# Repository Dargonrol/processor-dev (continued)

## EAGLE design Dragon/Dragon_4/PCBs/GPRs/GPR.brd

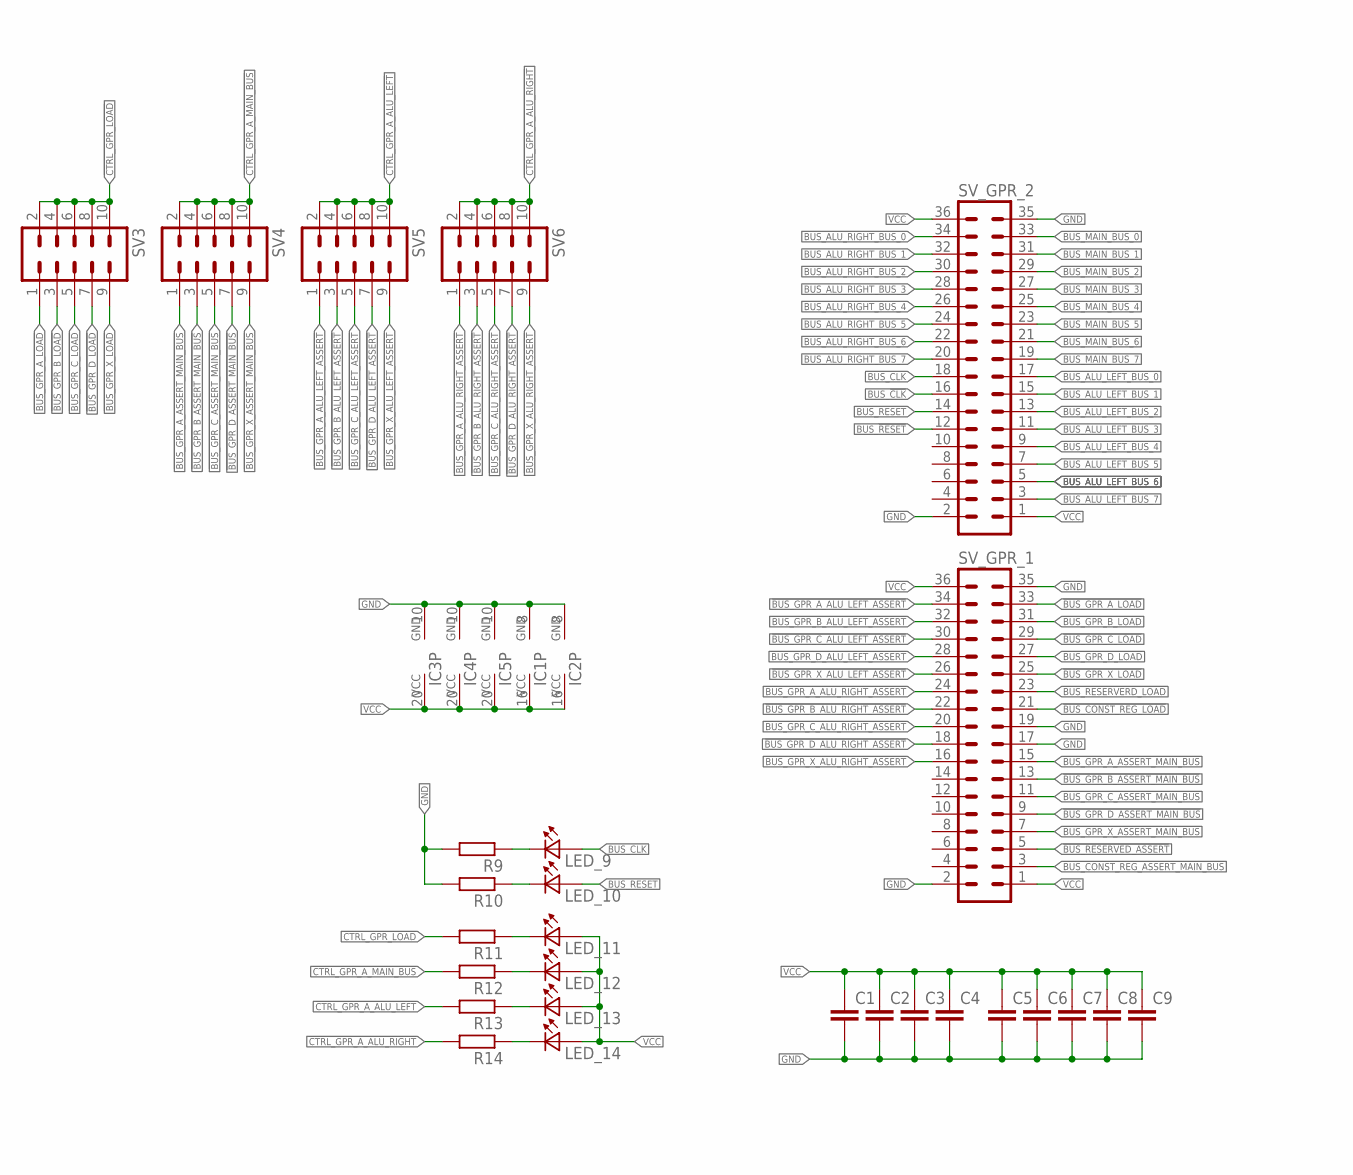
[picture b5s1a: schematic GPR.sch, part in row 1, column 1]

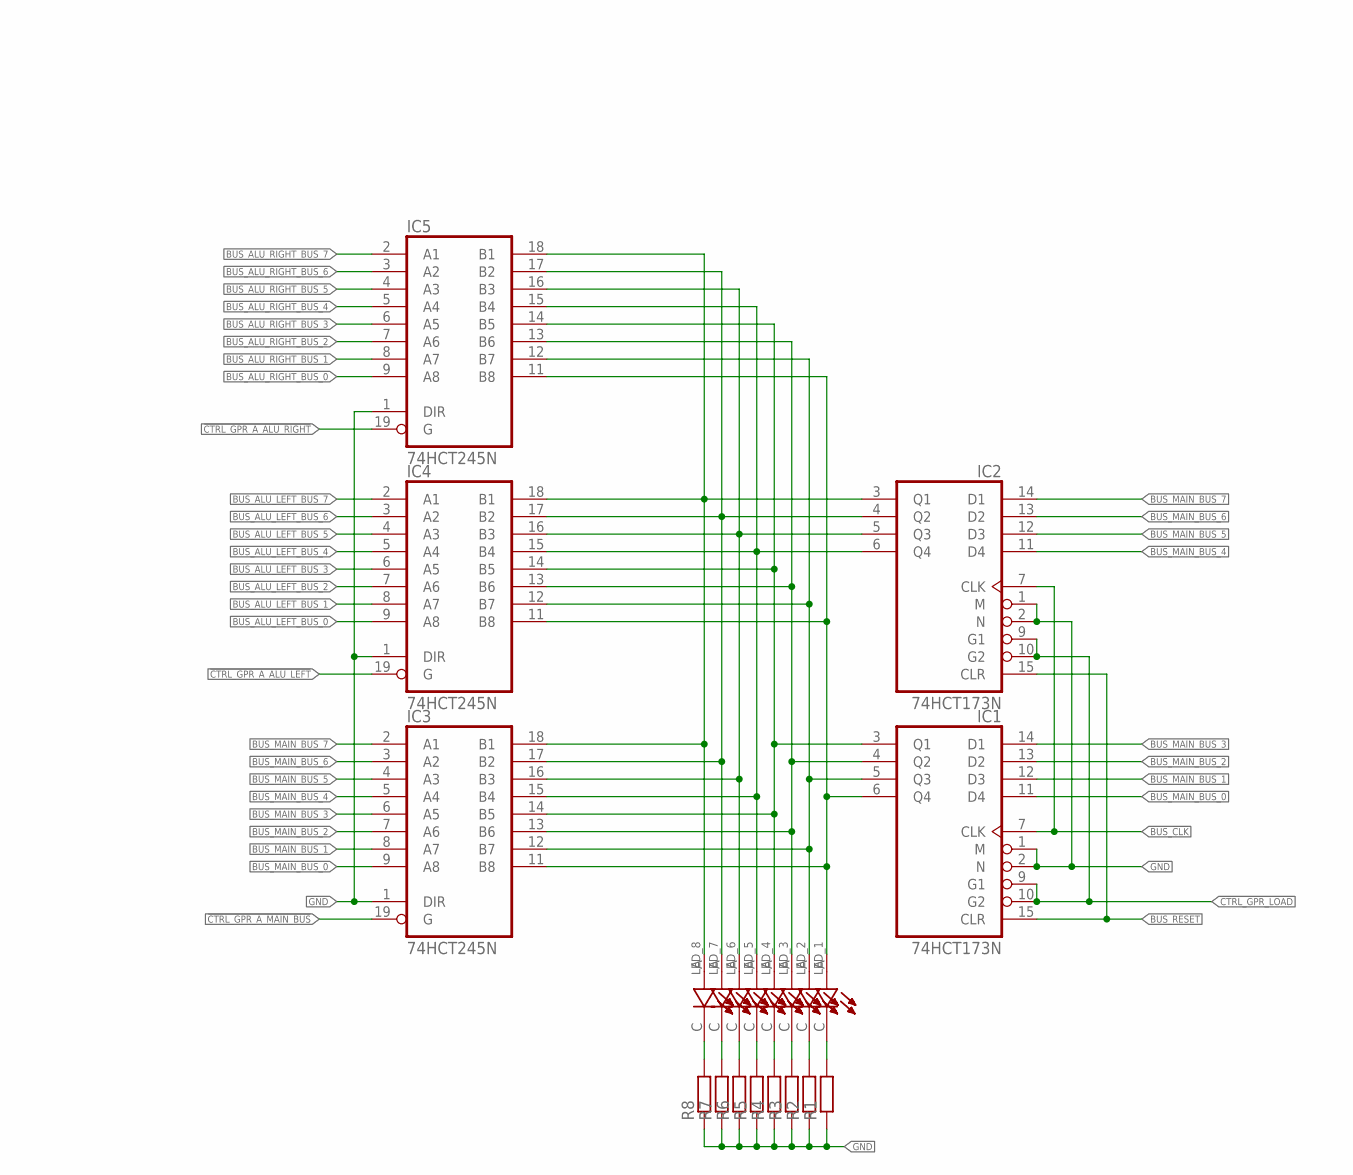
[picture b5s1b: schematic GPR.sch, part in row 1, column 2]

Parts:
C1, C2, C3, C4, C5, C6, C7, C8, C9: C-EUC0805; C0805
IC1, IC2: 74HCT173N; DIL16
IC3, IC4, IC5: 74HCT245N; DIL20
LED_1, LED_2, LED_3, LED_4, LED_5, LED_6, LED_7, LED_8: LTST-C193KRKT-5A; LEDC1608X45N
LED_9, LED_10, LED_11, LED_12, LED_13, LED_14: LTST-C193TBKT-5A; 0603
R1, R2, R3, R4, R5, R6, R7, R8, R9, R10, R11, R12, R13, R14: R-EU_R0805; R0805
SV3, SV4, SV5, SV6: MA05-2
SV_GPR_1, SV_GPR_2: MA18-2

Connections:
!BUS_CONST_REG_ASSERT_MAIN_BUS: SV_GPR_1.3
!BUS_CONST_REG_LOAD: SV_GPR_1.21
!BUS_GPR_A_ALU_LEFT_ASSERT: SV5.1, SV_GPR_1.34
!BUS_GPR_A_ALU_RIGHT_ASSERT: SV6.1, SV_GPR_1.24
!BUS_GPR_A_ASSERT_MAIN_BUS: SV4.1, SV_GPR_1.15
!BUS_GPR_A_LOAD: SV3.1, SV_GPR_1.33
!BUS_GPR_B_ALU_LEFT_ASSERT: SV5.3, SV_GPR_1.32
!BUS_GPR_B_ALU_RIGHT_ASSERT: SV6.3, SV_GPR_1.22
!BUS_GPR_B_ASSERT_MAIN_BUS: SV4.3, SV_GPR_1.13
!BUS_GPR_B_LOAD: SV3.3, SV_GPR_1.31
!BUS_GPR_C_ALU_LEFT_ASSERT: SV5.5, SV_GPR_1.30
!BUS_GPR_C_ALU_RIGHT_ASSERT: SV6.5, SV_GPR_1.20
!BUS_GPR_C_ASSERT_MAIN_BUS: SV4.5, SV_GPR_1.11
!BUS_GPR_C_LOAD: SV3.5, SV_GPR_1.29
!BUS_GPR_D_ALU_LEFT_ASSERT: SV5.7, SV_GPR_1.28
!BUS_GPR_D_ALU_RIGHT_ASSERT: SV6.7, SV_GPR_1.18
!BUS_GPR_D_ASSERT_MAIN_BUS: SV4.7, SV_GPR_1.9
!BUS_GPR_D_LOAD: SV3.7, SV_GPR_1.27
!BUS_GPR_X_ALU_LEFT_ASSERT: SV5.9, SV_GPR_1.26
!BUS_GPR_X_ALU_RIGHT_ASSERT: SV6.9, SV_GPR_1.16
!BUS_GPR_X_ASSERT_MAIN_BUS: SV4.9, SV_GPR_1.7
!BUS_GPR_X_LOAD: SV3.9, SV_GPR_1.25
!BUS_RESERVED_ASSERT: SV_GPR_1.5
!BUS_RESERVERD_LOAD: SV_GPR_1.23
!CTRL_GPR_A_ALU_LEFT: IC4.19 (G), R13.2, SV5.2, SV5.4, SV5.6, SV5.8, SV5.10
!CTRL_GPR_A_ALU_RIGHT: IC5.19 (G), R14.2, SV6.2, SV6.4, SV6.6, SV6.8, SV6.10
!CTRL_GPR_A_MAIN_BUS: IC3.19 (G), R12.2, SV4.2, SV4.4, SV4.6, SV4.8, SV4.10
!CTRL_GPR_LOAD: IC1.9 (G1), IC1.10 (G2), IC2.9 (G1), IC2.10 (G2), R11.2, SV3.2, SV3.4, SV3.6, SV3.8, SV3.10
BUS_!CLK: IC1.7 (CLK), IC2.7 (CLK), SV_GPR_2.16
BUS_!RESET: SV_GPR_2.12
BUS_ALU_LEFT_BUS_0: IC4.9 (A8), SV_GPR_2.17
BUS_ALU_LEFT_BUS_1: IC4.8 (A7), SV_GPR_2.15
BUS_ALU_LEFT_BUS_2: IC4.7 (A6), SV_GPR_2.13
BUS_ALU_LEFT_BUS_3: IC4.6 (A5), SV_GPR_2.11
BUS_ALU_LEFT_BUS_4: IC4.5 (A4), SV_GPR_2.9
BUS_ALU_LEFT_BUS_5: IC4.4 (A3), SV_GPR_2.7
BUS_ALU_LEFT_BUS_6: IC4.3 (A2), SV_GPR_2.5
BUS_ALU_LEFT_BUS_7: IC4.2 (A1), SV_GPR_2.3
BUS_ALU_RIGHT_BUS_0: IC5.9 (A8), SV_GPR_2.34
BUS_ALU_RIGHT_BUS_1: IC5.8 (A7), SV_GPR_2.32
BUS_ALU_RIGHT_BUS_2: IC5.7 (A6), SV_GPR_2.30
BUS_ALU_RIGHT_BUS_3: IC5.6 (A5), SV_GPR_2.28
BUS_ALU_RIGHT_BUS_4: IC5.5 (A4), SV_GPR_2.26
BUS_ALU_RIGHT_BUS_5: IC5.4 (A3), SV_GPR_2.24
BUS_ALU_RIGHT_BUS_6: IC5.3 (A2), SV_GPR_2.22
BUS_ALU_RIGHT_BUS_7: IC5.2 (A1), SV_GPR_2.20
BUS_CLK: LED_9.2 (A2), SV_GPR_2.18
BUS_MAIN_BUS_0: IC1.11 (D4), IC3.9 (A8), SV_GPR_2.33
BUS_MAIN_BUS_1: IC1.12 (D3), IC3.8 (A7), SV_GPR_2.31
BUS_MAIN_BUS_2: IC1.13 (D2), IC3.7 (A6), SV_GPR_2.29
BUS_MAIN_BUS_3: IC1.14 (D1), IC3.6 (A5), SV_GPR_2.27
BUS_MAIN_BUS_4: IC2.11 (D4), IC3.5 (A4), SV_GPR_2.25
BUS_MAIN_BUS_5: IC2.12 (D3), IC3.4 (A3), SV_GPR_2.23
BUS_MAIN_BUS_6: IC2.13 (D2), IC3.3 (A2), SV_GPR_2.21
BUS_MAIN_BUS_7: IC2.14 (D1), IC3.2 (A1), SV_GPR_2.19
BUS_RESET: IC1.15 (CLR), IC2.15 (CLR), LED_10.2 (A2), SV_GPR_2.14
GND: C1.2, C2.2, C3.2, C4.2, C5.2, C6.2, C7.2, C8.2, C9.2, IC1.1 (M), IC1.2 (N), IC1.8 (GND), IC2.1 (M), IC2.2 (N), IC2.8 (GND), IC3.1 (DIR), IC3.10 (GND), IC4.1 (DIR), IC4.10 (GND), IC5.1 (DIR), IC5.10 (GND), R1.1, R2.1, R3.1, R4.1, R5.1, R6.1, R7.1, R8.1, R9.2, R10.2, SV_GPR_1.2, SV_GPR_1.17, SV_GPR_1.19, SV_GPR_1.35, SV_GPR_2.2, SV_GPR_2.35
unnamed: LED_9.1 (K2), R9.1
unnamed: LED_10.1 (K2), R10.1
unnamed: LED_11.1 (K2), R11.1
unnamed: LED_12.1 (K2), R12.1
unnamed: LED_13.1 (K2), R13.1
unnamed: LED_1.C, R1.2
unnamed: LED_2.C, R2.2
unnamed: LED_3.C, R3.2
unnamed: LED_4.C, R4.2
unnamed: LED_5.C, R5.2
unnamed: LED_6.C, R6.2
unnamed: LED_7.C, R7.2
unnamed: LED_8.C, R8.2
unnamed: LED_14.1 (K2), R14.1
unnamed: IC1.3 (Q1), IC3.14 (B5), IC4.14 (B5), IC5.14 (B5), LED_4.A
unnamed: IC2.4 (Q2), IC3.17 (B2), IC4.17 (B2), IC5.17 (B2), LED_7.A
unnamed: IC2.6 (Q4), IC3.15 (B4), IC4.15 (B4), IC5.15 (B4), LED_5.A
unnamed: IC2.5 (Q3), IC3.16 (B3), IC4.16 (B3), IC5.16 (B3), LED_6.A
unnamed: IC1.6 (Q4), IC3.11 (B8), IC4.11 (B8), IC5.11 (B8), LED_1.A
unnamed: IC1.5 (Q3), IC3.12 (B7), IC4.12 (B7), IC5.12 (B7), LED_2.A
unnamed: IC1.4 (Q2), IC3.13 (B6), IC4.13 (B6), IC5.13 (B6), LED_3.A
unnamed: IC2.3 (Q1), IC3.18 (B1), IC4.18 (B1), IC5.18 (B1), LED_8.A
VCC: C1.1, C2.1, C3.1, C4.1, C5.1, C6.1, C7.1, C8.1, C9.1, IC1.16 (VCC), IC2.16 (VCC), IC3.20 (VCC), IC4.20 (VCC), IC5.20 (VCC), LED_11.2 (A2), LED_12.2 (A2), LED_13.2 (A2), LED_14.2 (A2), SV_GPR_1.1, SV_GPR_1.36, SV_GPR_2.1, SV_GPR_2.36

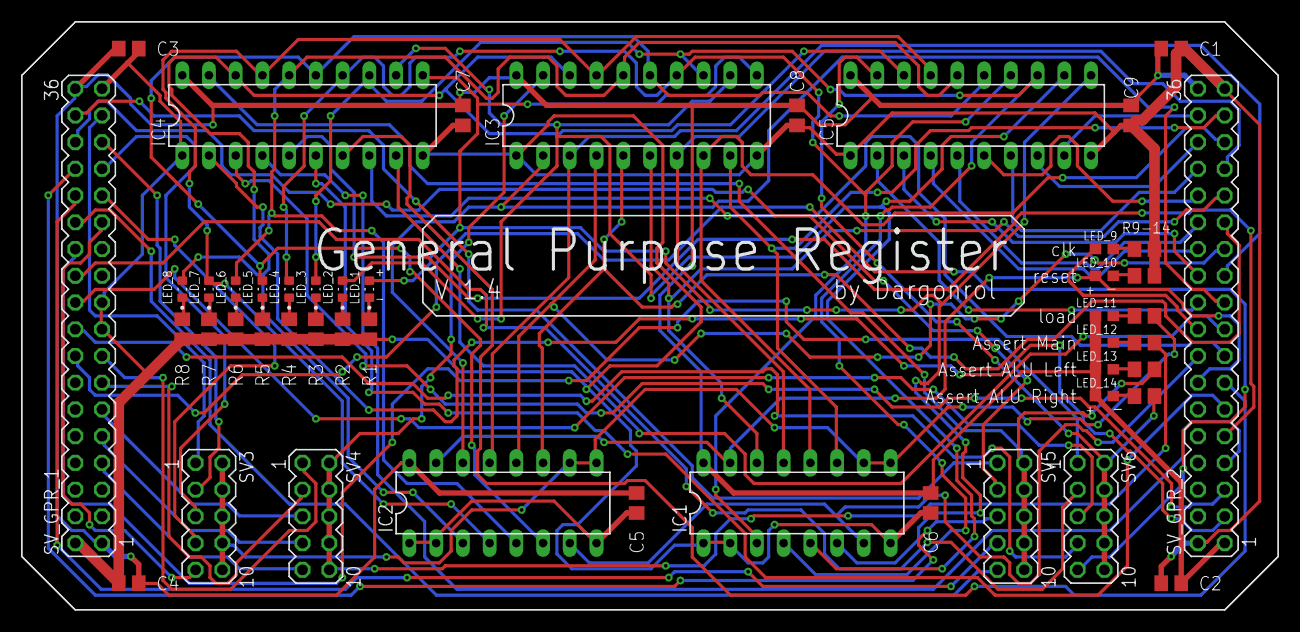
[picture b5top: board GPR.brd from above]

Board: 2 copper layers, 119.4 x 55.9 mm, 48 parts (0 on the bottom side), 75 nets.

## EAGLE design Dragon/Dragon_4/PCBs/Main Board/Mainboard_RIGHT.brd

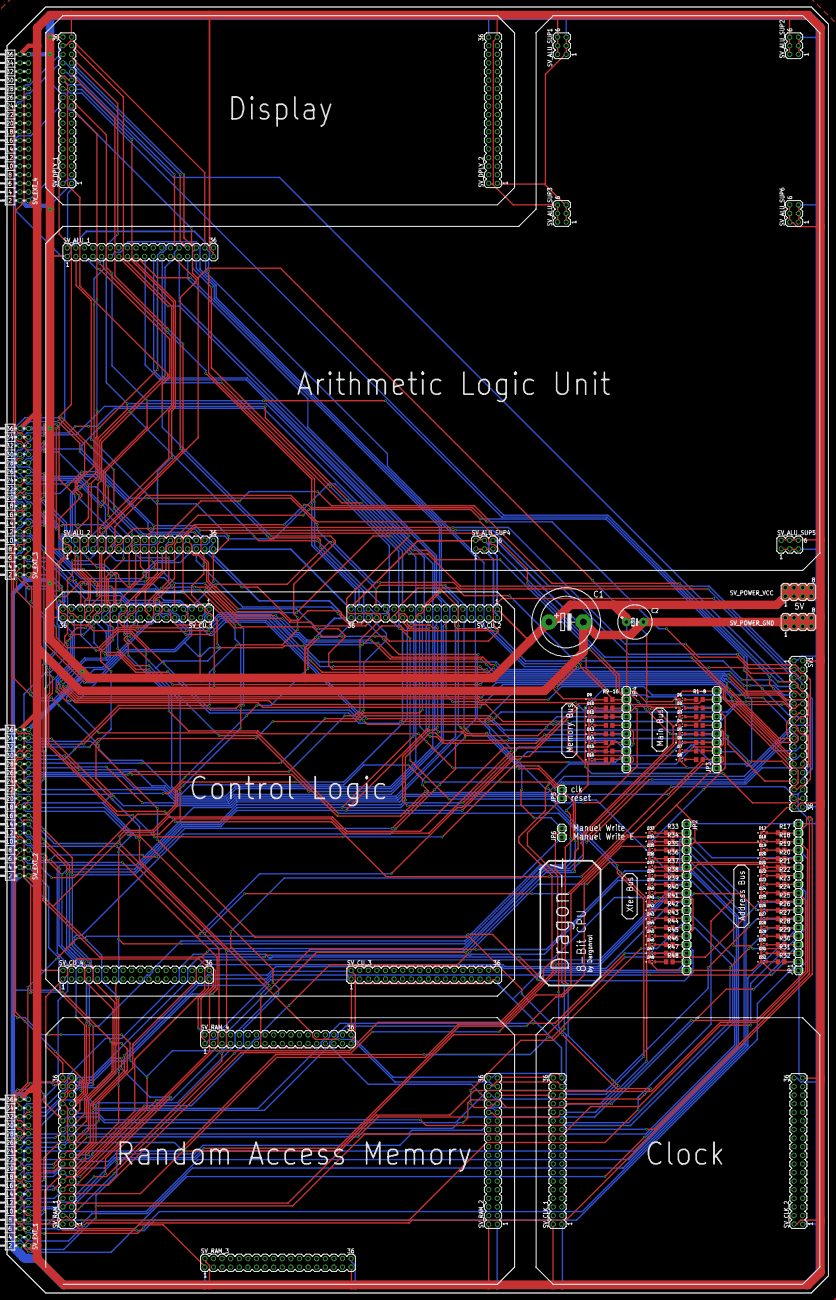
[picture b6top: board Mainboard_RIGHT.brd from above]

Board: 2 copper layers, 242.6 x 379.7 mm, 131 parts (0 on the bottom side), 160 nets.

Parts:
C1: EB20D
C2: E5-10,5
D1, D2, D3, D4, D5, D6, D7, D8, D9, D10, D11, D12, D13, D14, D15, D16, D17, D18, D19, D20, D21, D22, D23, D24, D25, D26, D27, D28, D29, D30, D31, D32, D33, D34, D35, D36, D37, D38, D39, D40, D41, D42, D43, D44, D45, D46, D47, D48: LTST-C193KRKT-5A; LEDC1608X45N
JP1, JP2: 1X18
JP3, JP4: 1X10
JP5, JP6: 1X02
R1, R2, R3, R4, R5, R6, R7, R8, R9, R10, R11, R12, R13, R14, R15, R16, R17, R18, R19, R20, R21, R22, R23, R24, R25, R26, R27, R28, R29, R30, R31, R32, R33, R34, R35, R36, R37, R38, R39, R40, R41, R42, R43, R44, R45, R46, R47, R48: R0805
SV1: MA18-2
SV_ALU_1, SV_ALU_2: MA18-2
SV_ALU_SUP1, SV_ALU_SUP2, SV_ALU_SUP3, SV_ALU_SUP4, SV_ALU_SUP5, SV_ALU_SUP6: MA03-2
SV_CLK_1, SV_CLK_2: MA18-2
SV_CU_1, SV_CU_2, SV_CU_3, SV_CU_4: MA18-2
SV_DPLY_1, SV_DPLY_2: MA18-2
SV_EXT_1, SV_EXT_2, SV_EXT_3, SV_EXT_4: MA18-2W
SV_POWER_GND: MA04-2
SV_POWER_VCC: MA04-2
SV_RAM_1, SV_RAM_2, SV_RAM_3, SV_RAM_4: MA18-2

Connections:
!CLK: SV_ALU_1.32, SV_CLK_1.31, SV_CU_2.31, SV_DPLY_1.32, SV_EXT_3.29, SV_RAM_2.32
!CTRL_ALU_ASSERT: SV_ALU_2.32, SV_EXT_3.23
!CTRL_DPLY_ENABLE: SV_DPLY_1.22, SV_EXT_3.15
!CTRL_IR_LOAD: SV_CU_2.23, SV_EXT_3.13
!CTRL_RAM_ASSERT_MAIN: SV_EXT_3.21, SV_RAM_2.31
!CTRL_RAM_LOAD_MAIN: SV_EXT_3.17, SV_RAM_2.33
!RESET: SV_ALU_1.28, SV_CLK_1.27, SV_CU_2.27, SV_DPLY_1.28, SV_EXT_3.25, SV_RAM_2.28
ADDRESS_BUS_0: JP1.2, R32.2, SV_EXT_1.34, SV_RAM_1.34
ADDRESS_BUS_1: JP1.3, R31.2, SV_EXT_1.32, SV_RAM_1.32
ADDRESS_BUS_2: JP1.4, R30.2, SV_EXT_1.30, SV_RAM_1.30
ADDRESS_BUS_3: JP1.5, R29.2, SV_EXT_1.28, SV_RAM_1.28
ADDRESS_BUS_4: JP1.6, R28.2, SV_EXT_1.26, SV_RAM_1.26
ADDRESS_BUS_5: JP1.7, R27.2, SV_EXT_1.24, SV_RAM_1.24
ADDRESS_BUS_6: JP1.8, R26.2, SV_EXT_1.22, SV_RAM_1.22
ADDRESS_BUS_7: JP1.9, R25.2, SV_EXT_1.20, SV_RAM_1.20
ADDRESS_BUS_8: JP1.10, R24.2, SV_EXT_1.18, SV_RAM_1.18
ADDRESS_BUS_9: JP1.11, R23.2, SV_EXT_1.16, SV_RAM_1.16
ADDRESS_BUS_10: JP1.12, R22.2, SV_EXT_1.14, SV_RAM_1.14
ADDRESS_BUS_11: JP1.13, R21.2, SV_EXT_1.12, SV_RAM_1.12
ADDRESS_BUS_12: JP1.14, R20.2, SV_EXT_1.10, SV_RAM_1.10
ADDRESS_BUS_13: JP1.15, R19.2, SV_EXT_1.8, SV_RAM_1.8
ADDRESS_BUS_14: JP1.16, R18.2, SV_EXT_1.6, SV_RAM_1.6
ADDRESS_BUS_15: JP1.17, R17.2, SV_EXT_1.4, SV_RAM_1.4
ALU_LEFT_BUS_0: SV_ALU_1.3, SV_EXT_2.34
ALU_LEFT_BUS_1: SV_ALU_1.5, SV_EXT_2.32
ALU_LEFT_BUS_2: SV_ALU_1.7, SV_EXT_2.30
ALU_LEFT_BUS_3: SV_ALU_1.9, SV_EXT_2.28
ALU_LEFT_BUS_4: SV_ALU_1.11, SV_EXT_2.26
ALU_LEFT_BUS_5: SV_ALU_1.13, SV_EXT_2.24
ALU_LEFT_BUS_6: SV_ALU_1.15, SV_EXT_2.22
ALU_LEFT_BUS_7: SV_ALU_1.17, SV_EXT_2.20
ALU_RIGHT_BUS_0: SV_ALU_1.19, SV_EXT_2.33
ALU_RIGHT_BUS_1: SV_ALU_1.21, SV_EXT_2.31
ALU_RIGHT_BUS_2: SV_ALU_1.23, SV_EXT_2.29
ALU_RIGHT_BUS_3: SV_ALU_1.25, SV_EXT_2.27
ALU_RIGHT_BUS_4: SV_ALU_1.27, SV_EXT_2.25
ALU_RIGHT_BUS_5: SV_ALU_1.29, SV_EXT_2.23
ALU_RIGHT_BUS_6: SV_ALU_1.31, SV_EXT_2.21
ALU_RIGHT_BUS_7: SV_ALU_1.33, SV_EXT_2.19
CLK: JP5.1, SV_ALU_1.34, SV_CLK_1.33, SV_CU_2.33, SV_DPLY_1.34, SV_EXT_3.31, SV_RAM_2.34
CTRL1_REG_A_1: SV1.3, SV_CU_1.3, SV_EXT_3.4
CTRL2_REG_A_2: SV1.5, SV_CU_1.5, SV_EXT_3.6
CTRL3_REG_A_3: SV1.7, SV_CU_1.7, SV_EXT_3.8
CTRL4_REG_A_4: SV1.9, SV_CU_1.9, SV_EXT_3.10
CTRL5_REG_L_1: SV1.11, SV_CU_1.11, SV_EXT_3.12
CTRL6_REG_L_2: SV1.13, SV_CU_1.13, SV_EXT_3.14
CTRL7_REG_L_3: SV1.15, SV_CU_1.15, SV_EXT_3.16
CTRL8_REG_L_4: SV1.17, SV_CU_1.17, SV_EXT_3.18
CTRL9_16REG_A_ADDR_1: SV1.19, SV_CU_1.19, SV_EXT_3.20
CTRL10_16REG_A_ADDR_2: SV1.21, SV_CU_1.21, SV_EXT_3.22
CTRL11_16REG_A_ADDR_3: SV1.23, SV_CU_1.23, SV_EXT_3.24
CTRL12_CREG_INC_1: SV1.25, SV_CU_1.25, SV_EXT_3.26
CTRL13_CREG_INC_2: SV1.27, SV_CU_1.27, SV_EXT_3.28
CTRL14_CREG_DEC_1: SV1.29, SV_CU_1.29, SV_EXT_3.30
CTRL15_CREG_DEC_2: SV1.31, SV_CU_1.31, SV_EXT_3.32
CTRL16_FLAGS: SV1.33, SV_ALU_2.34, SV_CU_1.33
CTRL17_GPR_A_ALU_R_1: SV1.4, SV_CU_1.4, SV_EXT_3.34
CTRL18_GPR_A_ALU_R_2: SV1.6, SV_CU_1.6, SV_EXT_3.3
CTRL19_GPR_A_ALU_R_3: SV1.8, SV_CU_1.8, SV_EXT_3.5
CTRL20_GPR_A_ALU_L_1: SV1.10, SV_CU_1.10, SV_EXT_3.7
CTRL21_GPR_A_ALU_L_2: SV1.12, SV_CU_1.12, SV_EXT_3.9
CTRL22_GPR_A_ALU_L_3: SV1.14, SV_CU_1.14, SV_EXT_3.11
CTRL23_NONE_1: SV1.16, SV_CU_1.16
CTRL24_NONE_2: SV1.18, SV_CU_1.18
CTRL25_ALU_OP_1: SV1.20, SV_ALU_2.24, SV_CU_1.20
CTRL26_ALU_OP_2: SV1.22, SV_ALU_2.26, SV_CU_1.22
CTRL27_ALU_OP_3: SV1.24, SV_ALU_2.28, SV_CU_1.24
CTRL28_ALU_OP_4: SV1.26, SV_ALU_2.30, SV_CU_1.26
CTRL29_DPLY_RS: SV1.28, SV_CU_1.28, SV_DPLY_1.24
CTRL30_DPLY_RW: SV1.30, SV_CU_1.30, SV_DPLY_1.26
CTRL31_HLT: SV1.32, SV_CLK_1.23, SV_CU_1.32
CTRL32_RST_STEP: SV1.34, SV_CU_1.34
CTRL_MANUAL_WRITE: JP6.2, SV_CU_2.19, SV_RAM_2.29
CTRL_MANUAL_WRITE_ENABLE: JP6.1, SV_RAM_2.27
FLAGS_1: SV_ALU_2.33, SV_CU_2.34
FLAGS_2: SV_ALU_2.31, SV_CU_2.32
FLAGS_3: SV_ALU_2.29, SV_CU_2.30
GND: C1.-, C2.-, D1.C, D2.C, D3.C, D4.C, D5.C, D6.C, D7.C, D8.C, D9.C, D10.C, D11.C, D12.C, D13.C, D14.C, D15.C, D16.C, D17.C, D18.C, D19.C, D20.C, D21.C, D22.C, D23.C, D24.C, D25.C, D26.C, D27.C, D28.C, D29.C, D30.C, D31.C, D32.C, D33.C, D34.C, D35.C, D36.C, D37.C, D38.C, D39.C, D40.C, D41.C, D42.C, D43.C, D44.C, D45.C, D46.C, D47.C, D48.C, JP1.1, JP2.18, JP3.1, JP4.10, SV1.2, SV1.35, SV_ALU_1.2, SV_ALU_1.35, SV_ALU_2.2, SV_ALU_2.35, SV_ALU_SUP1.2, SV_ALU_SUP1.4, SV_ALU_SUP1.6, SV_ALU_SUP2.2, SV_ALU_SUP2.4, SV_ALU_SUP2.6, SV_ALU_SUP3.2, SV_ALU_SUP3.4, SV_ALU_SUP3.6, SV_ALU_SUP4.2, SV_ALU_SUP4.4, SV_ALU_SUP4.6, SV_ALU_SUP5.2, SV_ALU_SUP5.4, SV_ALU_SUP5.6, SV_ALU_SUP6.2, SV_ALU_SUP6.4, SV_ALU_SUP6.6, SV_CLK_1.2, SV_CLK_1.35, SV_CLK_2.2, SV_CLK_2.35, SV_CU_1.2, SV_CU_1.35, SV_CU_2.2, SV_CU_2.35, SV_CU_3.2, SV_CU_3.35, SV_CU_4.2, SV_CU_4.35, SV_DPLY_1.2, SV_DPLY_1.35, SV_DPLY_2.2, SV_DPLY_2.35, SV_EXT_1.1, SV_EXT_1.36, SV_EXT_2.1, SV_EXT_2.36, SV_EXT_3.1, SV_EXT_3.36, SV_EXT_4.1, SV_EXT_4.36, SV_POWER_GND.1, SV_POWER_GND.2, SV_POWER_GND.3, SV_POWER_GND.4, SV_POWER_GND.5, SV_POWER_GND.6, SV_POWER_GND.7, SV_POWER_GND.8, SV_RAM_1.2, SV_RAM_1.35, SV_RAM_2.2, SV_RAM_2.35, SV_RAM_3.2, SV_RAM_3.35, SV_RAM_4.2, SV_RAM_4.35
MAIN_BUS_0: JP3.2, R8.2, SV_ALU_2.17, SV_DPLY_1.19, SV_EXT_2.18, SV_RAM_1.3
MAIN_BUS_1: JP3.3, R7.2, SV_ALU_2.15, SV_DPLY_1.21, SV_EXT_2.16, SV_RAM_1.5
MAIN_BUS_2: JP3.4, R6.2, SV_ALU_2.13, SV_DPLY_1.23, SV_EXT_2.14, SV_RAM_1.7
MAIN_BUS_3: JP3.5, R5.2, SV_ALU_2.11, SV_DPLY_1.25, SV_EXT_2.12, SV_RAM_1.9
MAIN_BUS_4: JP3.6, R4.2, SV_ALU_2.9, SV_DPLY_1.27, SV_EXT_2.10, SV_RAM_1.11
MAIN_BUS_5: JP3.7, R3.2, SV_ALU_2.7, SV_DPLY_1.29, SV_EXT_2.8, SV_RAM_1.13
MAIN_BUS_6: JP3.8, R2.2, SV_ALU_2.5, SV_DPLY_1.31, SV_EXT_2.6, SV_RAM_1.15
MAIN_BUS_7: JP3.9, R1.2, SV_ALU_2.3, SV_DPLY_1.33, SV_EXT_2.4, SV_RAM_1.17
MEMORY_BUS_0: JP4.9, R16.2, SV_CU_2.26, SV_EXT_2.17, SV_RAM_1.19
MEMORY_BUS_1: JP4.8, R15.2, SV_CU_2.24, SV_EXT_2.15, SV_RAM_1.21
MEMORY_BUS_2: JP4.7, R14.2, SV_CU_2.22, SV_EXT_2.13, SV_RAM_1.23
MEMORY_BUS_3: JP4.6, R13.2, SV_CU_2.20, SV_EXT_2.11, SV_RAM_1.25
MEMORY_BUS_4: JP4.5, R12.2, SV_CU_2.18, SV_EXT_2.9, SV_RAM_1.27
MEMORY_BUS_5: JP4.4, R11.2, SV_CU_2.16, SV_EXT_2.7, SV_RAM_1.29
MEMORY_BUS_6: JP4.3, R10.2, SV_CU_2.14, SV_EXT_2.5, SV_RAM_1.31
MEMORY_BUS_7: JP4.2, R9.2, SV_CU_2.12, SV_EXT_2.3, SV_RAM_1.33
unnamed: D1.A, R1.1
unnamed: D2.A, R2.1
unnamed: D3.A, R3.1
unnamed: D4.A, R4.1
unnamed: D5.A, R5.1
unnamed: D6.A, R6.1
unnamed: D7.A, R7.1
unnamed: D8.A, R8.1
unnamed: D9.A, R9.1
unnamed: D10.A, R10.1
unnamed: D11.A, R11.1
unnamed: D12.A, R12.1
unnamed: D13.A, R13.1
unnamed: D14.A, R14.1
unnamed: D15.A, R15.1
unnamed: D16.A, R16.1
unnamed: D17.A, R17.1
unnamed: D18.A, R18.1
unnamed: D19.A, R19.1
unnamed: D20.A, R20.1
unnamed: D21.A, R21.1
unnamed: D22.A, R22.1
unnamed: D23.A, R23.1
unnamed: D24.A, R24.1
unnamed: D25.A, R25.1
unnamed: D26.A, R26.1
unnamed: D27.A, R27.1
unnamed: D28.A, R28.1
unnamed: D29.A, R29.1
unnamed: D30.A, R30.1
unnamed: D31.A, R31.1
unnamed: D32.A, R32.1
unnamed: D33.A, R33.1
unnamed: D34.A, R34.1
unnamed: D35.A, R35.1
unnamed: D36.A, R36.1
unnamed: D37.A, R37.1
unnamed: D38.A, R38.1
unnamed: D39.A, R39.1
unnamed: D40.A, R40.1
unnamed: D41.A, R41.1
unnamed: D42.A, R42.1
unnamed: D43.A, R43.1
unnamed: D44.A, R44.1
unnamed: D45.A, R45.1
unnamed: D46.A, R46.1
unnamed: D47.A, R47.1
unnamed: D48.A, R48.1
RESET: JP5.2, SV_ALU_1.30, SV_CLK_1.29, SV_CU_2.29, SV_DPLY_1.30, SV_EXT_3.27, SV_RAM_2.30
VCC: C1.+, C2.+, JP1.18, JP2.1, JP3.10, JP4.1, SV1.1, SV1.36, SV_ALU_1.1, SV_ALU_1.36, SV_ALU_2.1, SV_ALU_2.36, SV_ALU_SUP1.1, SV_ALU_SUP1.3, SV_ALU_SUP1.5, SV_ALU_SUP2.1, SV_ALU_SUP2.3, SV_ALU_SUP2.5, SV_ALU_SUP3.1, SV_ALU_SUP3.3, SV_ALU_SUP3.5, SV_ALU_SUP4.1, SV_ALU_SUP4.3, SV_ALU_SUP4.5, SV_ALU_SUP5.1, SV_ALU_SUP5.3, SV_ALU_SUP5.5, SV_ALU_SUP6.1, SV_ALU_SUP6.3, SV_ALU_SUP6.5, SV_CLK_1.1, SV_CLK_1.36, SV_CLK_2.1, SV_CLK_2.36, SV_CU_1.1, SV_CU_1.36, SV_CU_2.1, SV_CU_2.36, SV_CU_3.1, SV_CU_3.36, SV_CU_4.1, SV_CU_4.36, SV_DPLY_1.1, SV_DPLY_1.36, SV_DPLY_2.1, SV_DPLY_2.36, SV_EXT_1.2, SV_EXT_1.35, SV_EXT_2.2, SV_EXT_2.35, SV_EXT_3.2, SV_EXT_3.35, SV_EXT_4.2, SV_EXT_4.35, SV_POWER_VCC.1, SV_POWER_VCC.2, SV_POWER_VCC.3, SV_POWER_VCC.4, SV_POWER_VCC.5, SV_POWER_VCC.6, SV_POWER_VCC.7, SV_POWER_VCC.8, SV_RAM_1.1, SV_RAM_1.36, SV_RAM_2.1, SV_RAM_2.36, SV_RAM_3.1, SV_RAM_3.36, SV_RAM_4.1, SV_RAM_4.36
XFER_BUS_0: JP2.17, R48.2, SV_EXT_1.33
XFER_BUS_1: JP2.16, R47.2, SV_EXT_1.31
XFER_BUS_2: JP2.15, R46.2, SV_EXT_1.29
XFER_BUS_3: JP2.14, R45.2, SV_EXT_1.27
XFER_BUS_4: JP2.13, R44.2, SV_EXT_1.25
XFER_BUS_5: JP2.12, R43.2, SV_EXT_1.23
XFER_BUS_6: JP2.11, R42.2, SV_EXT_1.21
XFER_BUS_7: JP2.10, R41.2, SV_EXT_1.19
XFER_BUS_8: JP2.9, R40.2, SV_EXT_1.17
XFER_BUS_9: JP2.8, R39.2, SV_EXT_1.15
XFER_BUS_10: JP2.7, R38.2, SV_EXT_1.13
XFER_BUS_11: JP2.6, R37.2, SV_EXT_1.11
XFER_BUS_12: JP2.5, R36.2, SV_EXT_1.9
XFER_BUS_13: JP2.4, R35.2, SV_EXT_1.7
XFER_BUS_14: JP2.3, R34.2, SV_EXT_1.5
XFER_BUS_15: JP2.2, R33.2, SV_EXT_1.3

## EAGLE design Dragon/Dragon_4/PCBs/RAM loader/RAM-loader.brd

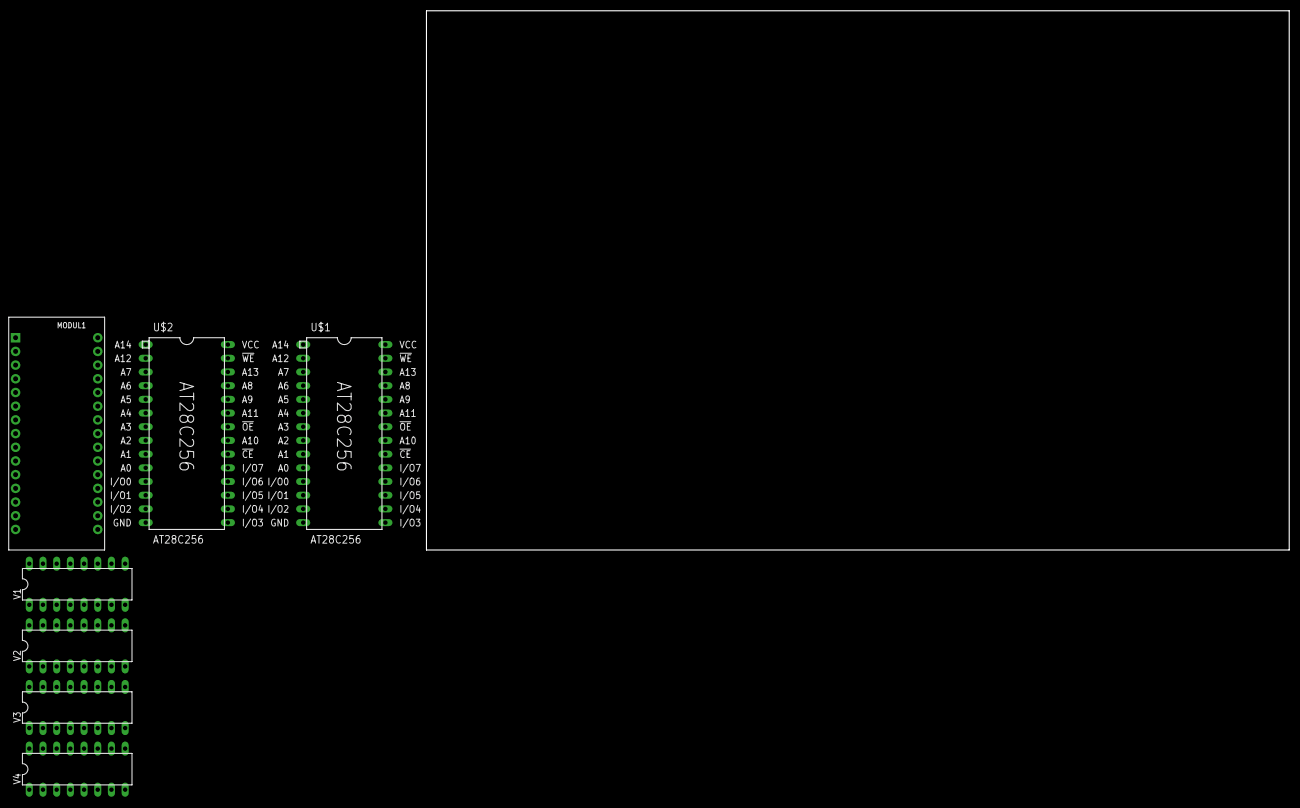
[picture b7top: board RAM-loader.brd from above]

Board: 2 copper layers, 160.0 x 100.0 mm, 7 parts (0 on the bottom side), 2 nets, no tracks yet.

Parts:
MODUL1: ARDUINO_NANO; ARDUINO_NANO2
U$1, U$2: AT28C256
V1, V2, V3, V4: 74193N; DIL16

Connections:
+UB: V1.16, V2.16, V3.16, V4.16
-UB: V1.8, V2.8, V3.8, V4.8

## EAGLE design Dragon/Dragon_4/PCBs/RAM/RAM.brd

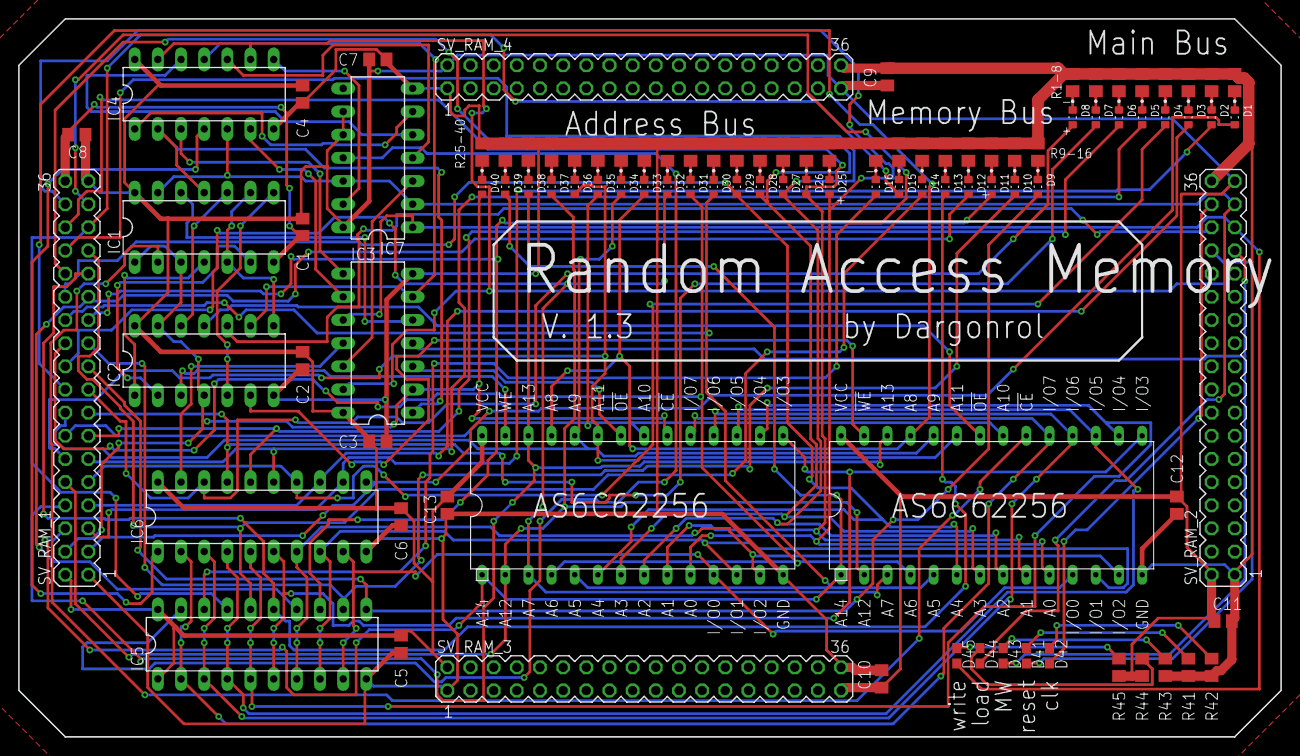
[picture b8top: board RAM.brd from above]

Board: 2 copper layers, 138.4 x 78.7 mm, 100 parts (0 on the bottom side), 109 nets.

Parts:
C1, C2, C3, C4, C5, C6, C7, C8, C9, C10, C11, C12, C13: C0805
D1, D2, D3, D4, D5, D6, D7, D8, D9, D10, D11, D12, D13, D14, D15, D16, D25, D26, D27, D28, D29, D30, D31, D32, D33, D34, D35, D36, D37, D38, D39, D40: LTST-C193KRKT-5A; LEDC1608X45N
D41, D42, D43, D44, D45: LTST-C193TBKT-5A; 0603
IC1, IC4: 74HCT04N; DIL14
IC2: 74HCT00N; DIL14
IC3: 74HCT32N; DIL14
IC5, IC6: 74HCT245N; DIL20
IC7: 74HCT08N; DIL14
R1, R2, R3, R4, R5, R6, R7, R8, R9, R10, R11, R12, R13, R14, R15, R16, R25, R26, R27, R28, R29, R30, R31, R32, R33, R34, R35, R36, R37, R38, R39, R40, R41, R42, R43, R44, R45: R0805
SV_RAM_1, SV_RAM_2, SV_RAM_3, SV_RAM_4: MA18-2
U$1, U$2: AS6C62256

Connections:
!CTRL_RAM_ASSERT_MAIN: D45.1, IC3.10, IC7.1, SV_RAM_2.31
!CTRL_RAM_LOAD_MAIN: D44.1, IC1.13, IC4.5, IC7.2, IC7.12, SV_RAM_2.33
BUS_!CLK: IC2.10, SV_RAM_2.32
BUS_ADDRESS_BUS_0: D25.A, SV_RAM_1.34, U$1.A0, U$2.A0
BUS_ADDRESS_BUS_1: D26.A, SV_RAM_1.32, U$1.A1, U$2.A1
BUS_ADDRESS_BUS_2: D27.A, SV_RAM_1.30, U$1.A2, U$2.A2
BUS_ADDRESS_BUS_3: D28.A, SV_RAM_1.28, U$1.A3, U$2.A3
BUS_ADDRESS_BUS_4: D29.A, SV_RAM_1.26, U$1.A4, U$2.A4
BUS_ADDRESS_BUS_5: D30.A, SV_RAM_1.24, U$1.A5, U$2.A5
BUS_ADDRESS_BUS_6: D31.A, SV_RAM_1.22, U$1.A6, U$2.A6
BUS_ADDRESS_BUS_7: D32.A, SV_RAM_1.20, U$1.A7, U$2.A7
BUS_ADDRESS_BUS_8: D33.A, SV_RAM_1.18, U$1.A8, U$2.A8
BUS_ADDRESS_BUS_9: D34.A, SV_RAM_1.16, U$1.A9, U$2.A9
BUS_ADDRESS_BUS_10: D35.A, SV_RAM_1.14, U$1.A10, U$2.A10
BUS_ADDRESS_BUS_11: D36.A, SV_RAM_1.12, U$1.A11, U$2.A11
BUS_ADDRESS_BUS_12: D37.A, SV_RAM_1.10, U$1.A12, U$2.A12
BUS_ADDRESS_BUS_13: D38.A, SV_RAM_1.8, U$1.A13, U$2.A13
BUS_ADDRESS_BUS_14: D39.A, SV_RAM_1.6, U$1.A14, U$2.A14
BUS_ADDRESS_BUS_15: D40.A, IC1.1, IC1.3, IC2.4, IC2.13, IC3.2, SV_RAM_1.4, U$1.!CE
BUS_CLK: D42.2, SV_RAM_2.34
BUS_MAIN_BUS_0: D1.A, IC6.11, SV_RAM_1.3
BUS_MAIN_BUS_1: D2.A, IC6.12, SV_RAM_1.5
BUS_MAIN_BUS_2: D3.A, IC6.13, SV_RAM_1.7
BUS_MAIN_BUS_3: D4.A, IC6.14, SV_RAM_1.9
BUS_MAIN_BUS_4: D5.A, IC6.15, SV_RAM_1.11
BUS_MAIN_BUS_5: D6.A, IC6.16, SV_RAM_1.13
BUS_MAIN_BUS_6: D7.A, IC6.17, SV_RAM_1.15
BUS_MAIN_BUS_7: D8.A, IC6.18, SV_RAM_1.17
BUS_MEMORY_BUS_0: D9.A, IC5.11, SV_RAM_1.19
BUS_MEMORY_BUS_1: D10.A, IC5.12, SV_RAM_1.21
BUS_MEMORY_BUS_2: D11.A, IC5.13, SV_RAM_1.23
BUS_MEMORY_BUS_3: D12.A, IC5.14, SV_RAM_1.25
BUS_MEMORY_BUS_4: D13.A, IC5.15, SV_RAM_1.27
BUS_MEMORY_BUS_5: D14.A, IC5.16, SV_RAM_1.29
BUS_MEMORY_BUS_6: D15.A, IC5.17, SV_RAM_1.31
BUS_MEMORY_BUS_7: D16.A, IC5.18, SV_RAM_1.33
BUS_RESET: D41.2, SV_RAM_2.30
CTRL_MANUAL_WRITE: D43.2, IC3.4, SV_RAM_2.29
CTRL_MANUAL_WRITE_ENABLE: IC3.13, IC4.9, IC4.13, SV_RAM_2.27
GND: C1.2, C2.2, C3.2, C4.2, C5.2, C6.2, C7.2, C8.2, C9.2, C10.2, C11.2, C12.2, C13.2, IC1.7, IC2.7, IC3.7, IC4.7, IC5.10, IC6.10, IC7.7, R1.1, R2.1, R3.1, R4.1, R5.1, R6.1, R7.1, R8.1, R9.1, R10.1, R11.1, R12.1, R13.1, R14.1, R15.1, R16.1, R25.1, R26.1, R27.1, R28.1, R29.1, R30.1, R31.1, R32.1, R33.1, R34.1, R35.1, R36.1, R37.1, R38.1, R39.1, R40.1, R41.1, R42.1, R43.1, SV_RAM_1.1, SV_RAM_1.36, SV_RAM_2.1, SV_RAM_2.36, SV_RAM_3.1, SV_RAM_3.36, SV_RAM_4.1, SV_RAM_4.36, U$1.GND, U$2.GND
unnamed: IC5.2, IC6.2, U$1.I/O7, U$2.I/O7
unnamed: IC5.3, IC6.3, U$1.I/O6, U$2.I/O6
unnamed: IC5.4, IC6.4, U$1.I/O5, U$2.I/O5
unnamed: IC5.5, IC6.5, U$1.I/O4, U$2.I/O4
unnamed: IC5.6, IC6.6, U$1.I/O3, U$2.I/O3
unnamed: IC5.7, IC6.7, U$1.I/O2, U$2.I/O2
unnamed: IC5.8, IC6.8, U$1.I/O1, U$2.I/O1
unnamed: IC5.9, IC6.9, U$1.I/O0, U$2.I/O0
unnamed: IC3.8, IC4.3
unnamed: IC3.9, IC4.6
unnamed: D1.C, R1.2
unnamed: D2.C, R2.2
unnamed: IC4.4, IC6.1
unnamed: IC3.11, IC6.19
unnamed: IC1.10, IC2.12
unnamed: IC1.4, IC2.1
unnamed: IC1.2, U$2.!CE
unnamed: IC1.6, IC2.2
unnamed: IC2.3, U$1.!WE
unnamed: IC2.6, U$2.!WE
unnamed: IC1.8, IC2.5
unnamed: D3.C, R3.2
unnamed: IC1.5, IC1.9, IC2.8
unnamed: IC1.11, IC3.1, IC4.2
unnamed: IC2.11, U$2.!OE
unnamed: D4.C, R4.2
unnamed: IC3.3, U$1.!OE
unnamed: IC1.12, IC3.5
unnamed: D5.C, R5.2
unnamed: D6.C, R6.2
unnamed: D7.C, R7.2
unnamed: D8.C, R8.2
unnamed: D9.C, R9.2
unnamed: D10.C, R10.2
unnamed: D11.C, R11.2
unnamed: D12.C, R12.2
unnamed: D13.C, R13.2
unnamed: D14.C, R14.2
unnamed: D15.C, R15.2
unnamed: D16.C, R16.2
unnamed: IC3.12, IC7.3
unnamed: IC4.8, IC7.13
unnamed: IC2.9, IC3.6, IC4.11
unnamed: IC5.19, IC7.11
unnamed: IC4.1, IC7.6
unnamed: IC4.10, IC7.4
unnamed: IC4.12, IC7.5
unnamed: D25.C, R25.2
unnamed: D26.C, R26.2
unnamed: D27.C, R27.2
unnamed: D28.C, R28.2
unnamed: D29.C, R29.2
unnamed: D30.C, R30.2
unnamed: D31.C, R31.2
unnamed: D32.C, R32.2
unnamed: D33.C, R33.2
unnamed: D34.C, R34.2
unnamed: D35.C, R35.2
unnamed: D36.C, R36.2
unnamed: D37.C, R37.2
unnamed: D38.C, R38.2
unnamed: D39.C, R39.2
unnamed: D40.C, R40.2
unnamed: D41.1, R41.2
unnamed: D42.1, R42.2
unnamed: D43.1, R43.2
unnamed: D44.2, R44.2
unnamed: D45.2, R45.2
VCC: C1.1, C2.1, C3.1, C4.1, C5.1, C6.1, C7.1, C8.1, C9.1, C10.1, C11.1, C12.1, C13.1, IC1.14, IC2.14, IC3.14, IC4.14, IC5.1, IC5.20, IC6.20, IC7.9, IC7.10, IC7.14, R44.1, R45.1, SV_RAM_1.2, SV_RAM_1.35, SV_RAM_2.2, SV_RAM_2.35, SV_RAM_3.2, SV_RAM_3.35, SV_RAM_4.2, SV_RAM_4.35, U$1.VCC, U$2.VCC
